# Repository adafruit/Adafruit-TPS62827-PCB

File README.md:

## TPS62827 3.3V Buck Converter Breakout PCB

<a href="http://www.adafruit.com/products/4920"><br/>
Click here to purchase one from the Adafruit shop</a>

PCB files for the TPS62827 3.3V Buck Converter Breakout. 

Format is EagleCAD schematic and board layout
* https://www.adafruit.com/product/4920

### Description

This little buck converter based on the TPS62827 is super handy, taking up to 5.5V input and providing a 3.3V output with up to 2A current. It's great for supplying power to hungry 3.3V voltage circuits from a range of battery or power options.  This chip provides up to 2 Amp load current across the entire input voltage range of 3.4 to 5.5V. It's not a huge range but does cover LiPoly batteries, 3 alkalines, and USB power.

Great for your portable project, we made this "pin compatible" with the LM1117-3.3V TO-220 chip so you can swap it in for better performance (90-95% efficiency!) There's also an ENable pin, tie it low to shut down the output completely.

The Adafruit TPS62827 Breakout runs at 2.2-MHz fixed-frequency. Even though the chip itself supports up to 4A, we found that 2 Amps or so was a good max to stick to for constant current draw and 3 Amps for temporary peak current draws. We did use a 2 oz copper double-layer PCB.

If you need a wider input range, check out the 3.3V output MPM3610 breakout with up to 20V input!

Comes with a fully assembled and tested breakout board.  We also include header to plug it into a breadboard.

### License

Adafruit invests time and resources providing this open source design, please support Adafruit and open-source hardware by purchasing products from [Adafruit](https://www.adafruit.com)!

Designed by Limor Fried/Ladyada for Adafruit Industries.

Creative Commons Attribution/Share-Alike, all text above must be included in any redistribution. 
See license.txt for additional details.

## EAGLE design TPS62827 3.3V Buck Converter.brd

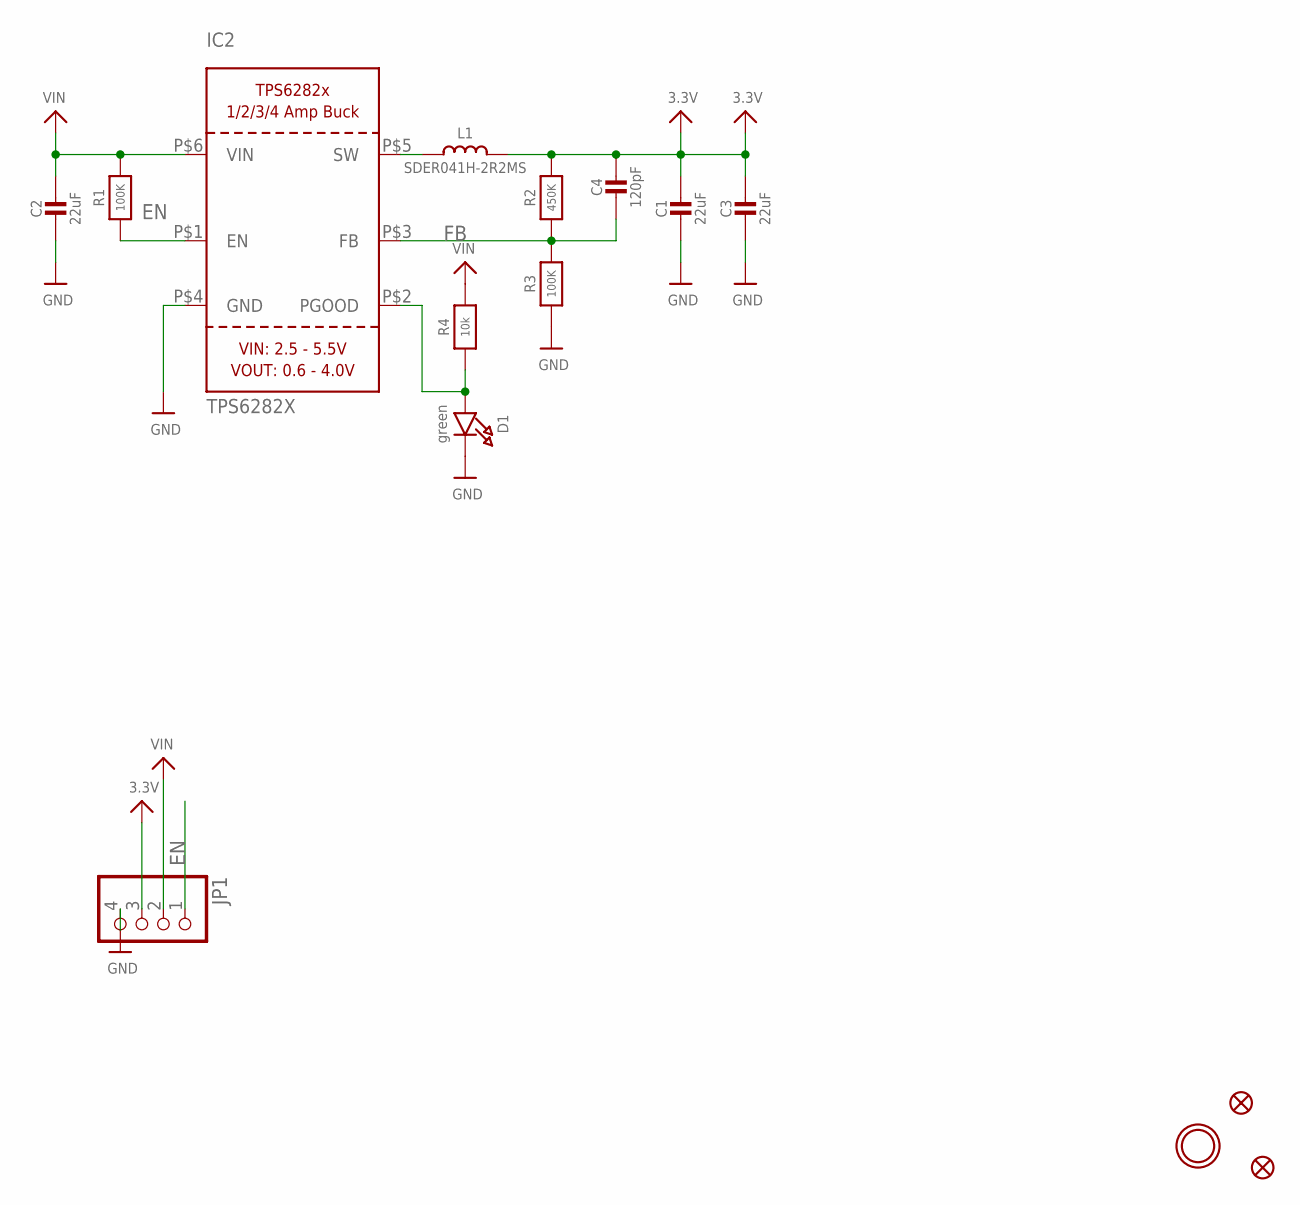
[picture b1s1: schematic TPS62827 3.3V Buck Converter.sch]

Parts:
C1, C2, C3: 22uF; 0805-NO
C4: 120pF; 0603-NO
D1: green; CHIPLED_0603_NOOUTLINE
FID1, FID2: FIDUCIAL_1MM
IC2: TPS6282X; VSON_6
JP1: HEADER-1X4ROUND; 1X04_ROUND
L1: SDER041H-2R2MS; INDUCTOR_4X4MM_SRP0415
R1, R3: 100K; 0603-NO
R2: 450K; 0603-NO
R4: 10k; _0603MP
U$9: MOUNTINGHOLE2.5; MOUNTINGHOLE_2.5_PLATED

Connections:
3.3V: C1.1, C3.1, C4.1, JP1.3, L1.P$2 (2), R2.2
EN: IC2.P$1 (EN), JP1.1, R1.2
FB: C4.2, IC2.P$3 (FB), R2.1, R3.2
GND: C1.2, C2.2, C3.2, D1.C, IC2.P$4 (GND), JP1.4, R3.1
unnamed: IC2.P$5 (SW), L1.P$1 (1)
unnamed: D1.A, IC2.P$2 (PGOOD), R4.1
VIN: C2.1, IC2.P$6 (VIN), JP1.2, R1.1, R4.2

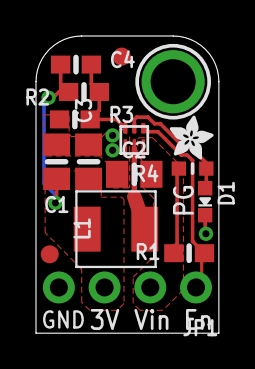
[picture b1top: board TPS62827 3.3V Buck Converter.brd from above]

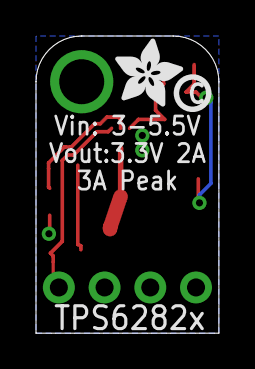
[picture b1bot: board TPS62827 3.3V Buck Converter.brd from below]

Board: 2 copper layers, 10.2 x 16.5 mm, 18 parts (2 on the bottom side), 7 nets.

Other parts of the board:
U$10: PCBFEAT-REV-040
U$11: ADAFRUIT_2.5MM
U$18: ADAFRUIT_3.5MM

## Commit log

2021-02-23 adding board files.

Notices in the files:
parts and their libraries:
microbuilder: This work is placed in the public domain, and may be freely used for commercial and non-commercial work with the following conditions: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
